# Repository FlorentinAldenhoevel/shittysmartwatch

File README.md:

# shittysmartwatch
A shitty, but hopfully decent ESP32 based Smartwatch

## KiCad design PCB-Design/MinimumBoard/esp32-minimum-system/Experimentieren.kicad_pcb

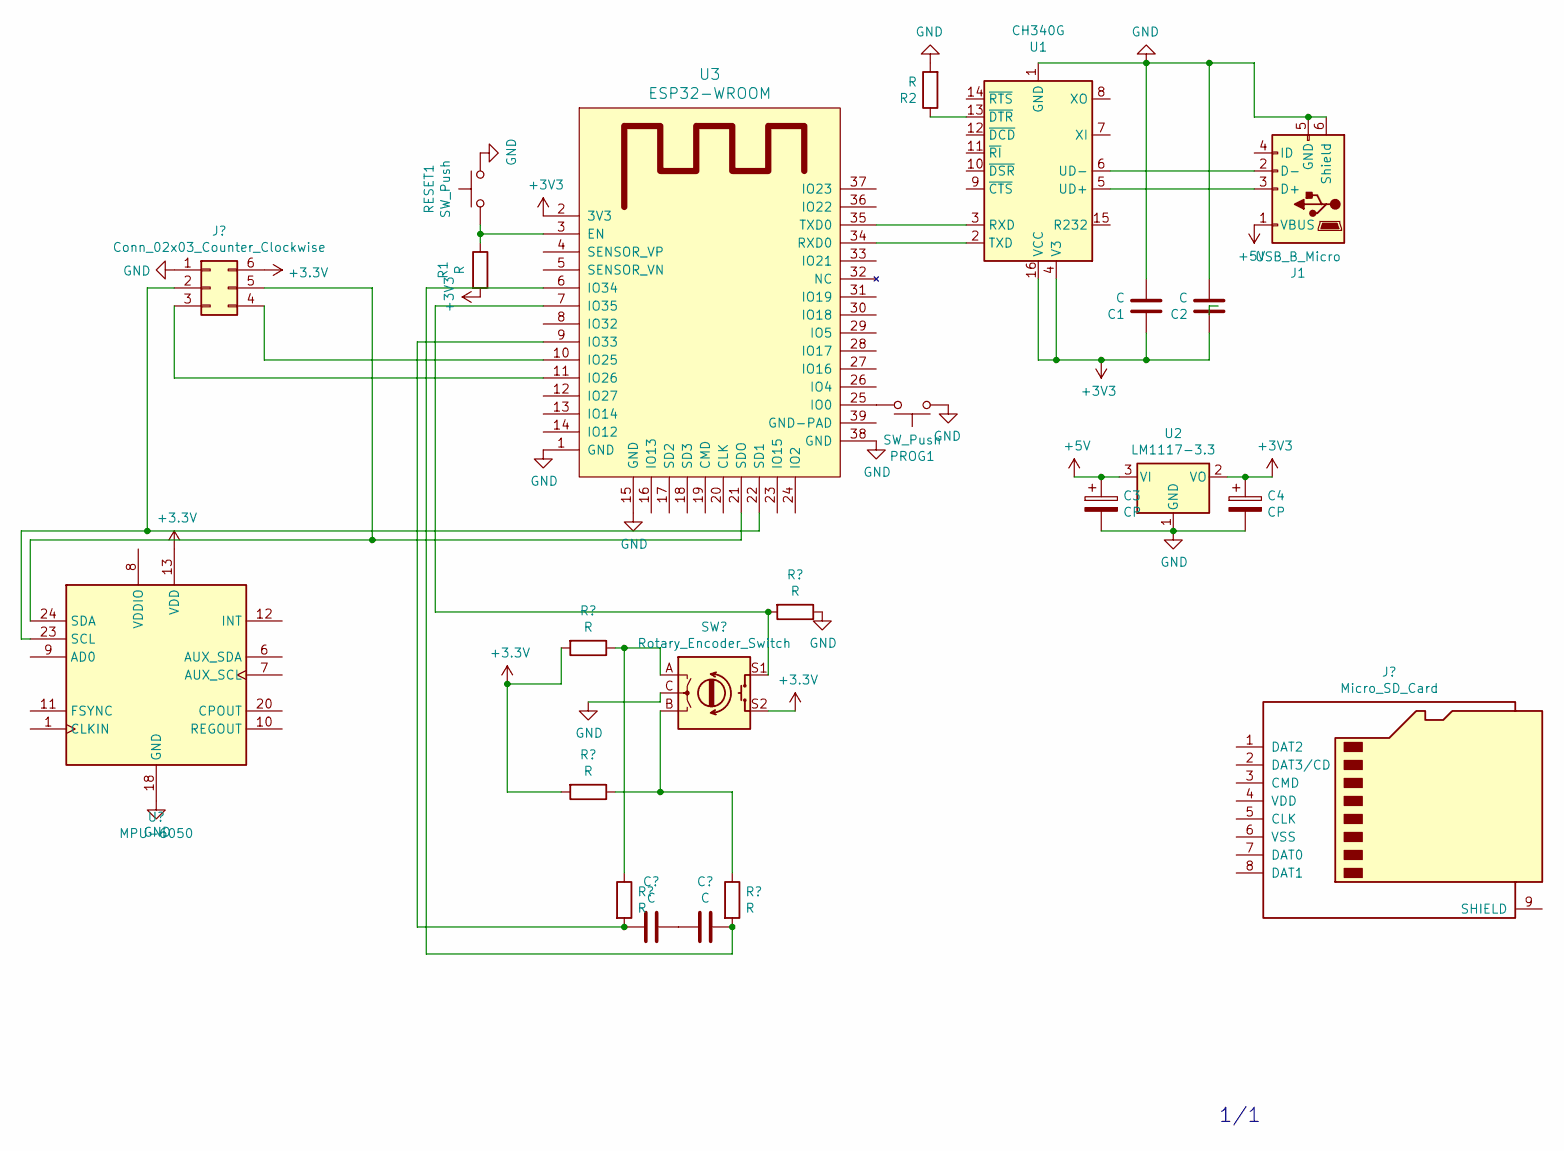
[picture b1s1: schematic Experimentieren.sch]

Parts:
C1, C2: C; C_1206_HandSoldering
C3, C4: CP; CP_Tantalum_Case-A_EIA-3216-18_Hand
J1: USB_B_Micro; USB_Micro-B
PROG1: SW_Push; SW_SPST_SKQG
R1, R2: R; R_1206_HandSoldering
RESET1: SW_Push; SW_SPST_SKQG
U1: CH340G; SOIC-16_3.9x9.9mm_Pitch1.27mm
U2: LM1117-3.3; SOT-223
U3: ESP32-WROOM

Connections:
+3V3: C1.1, C2.1, C4.1, R1.2, U1.4 (V3), U1.16 (VCC), U2.2 (VO), U3.2 (3V3)
+5V: C3.1, J1.1 (VBUS), U2.3 (VI)
GND: C1.2, C2.2, C3.2, C4.2, J1.5 (GND), J1.6 (Shield), PROG1.1, R2.2, RESET1.1, U1.1 (GND), U2.1 (GND), U3.1 (GND), U3.15 (GND), U3.38 (GND)
unnamed: J1.2 (D-), U1.6 (UD-)
unnamed: J1.3 (D+), U1.5 (UD+)
unnamed: PROG1.2, U3.25 (IO0)
unnamed: R1.1, RESET1.2, U3.3 (EN)
unnamed: R2.1, U1.13 (~DTR)
unnamed: U1.2 (TXD), U3.34 (RXD0)
unnamed: U1.3 (RXD), U3.35 (TXD0)

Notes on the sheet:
1/1

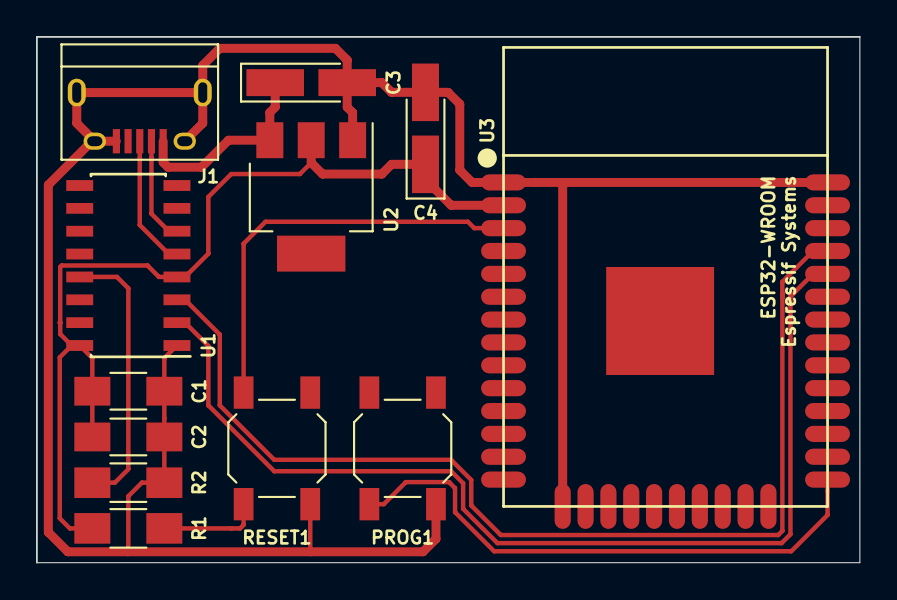
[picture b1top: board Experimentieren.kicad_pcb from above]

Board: 2 copper layers, 45.7 x 29.2 mm, 12 parts (0 on the bottom side), 10 nets.

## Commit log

2021-04-13 Menu navigation and Application return
2021-04-14 Modes for setting the time
